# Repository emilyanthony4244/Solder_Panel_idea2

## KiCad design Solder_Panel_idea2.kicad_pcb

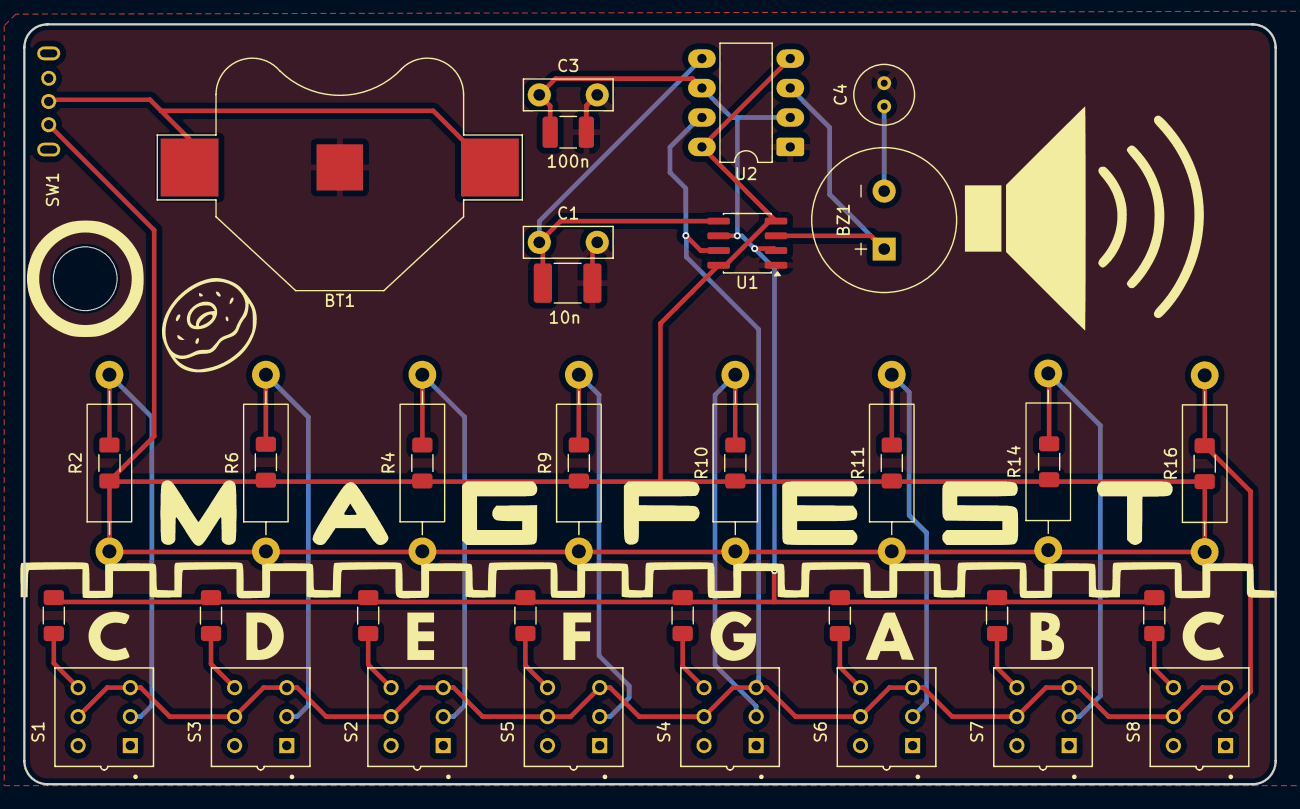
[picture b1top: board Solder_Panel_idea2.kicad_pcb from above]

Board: 2 copper layers, 107.9 x 65.5 mm, 42 parts (0 on the bottom side), 22 nets.

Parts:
BT1: 1043; BatteryHolder_Multicomp_BC-2001_1x2032
BZ1: Buzzer; Buzzer_12.5x7.5
C1: 10n; C_Disc_D7.5mm_W2.5mm_P5.00mm
C2: 100n; C_1210_3225Metric_Pad1.33x2.70mm_HandSolder
C3: 100n; C_Disc_D7.5mm_W2.5mm_P5.00mm
C4: 10u; C_Radial_D5.0mm_H7.0mm_P2.00mm
C5: 10n; C_1812_4532Metric_Pad1.57x3.40mm_HandSolder
R1, R3, R5, R7, R8, R12, R13, R15: 910; R_1206_3216Metric_Pad1.30x1.75mm_HandSolder
R2, R4, R6, R9, R10, R11, R14, R16: 910; R_Axial_DIN0411_L9.9mm_D3.6mm_P15.24mm_Horizontal
R17: 24k; R_1206_3216Metric_Pad1.30x1.75mm_HandSolder
R18: 27k; R_1206_3216Metric_Pad1.30x1.75mm_HandSolder
R19: 22k; R_1206_3216Metric_Pad1.30x1.75mm_HandSolder
R20: 18k; R_1206_3216Metric_Pad1.30x1.75mm_HandSolder
R21: 20k; R_1206_3216Metric_Pad1.30x1.75mm_HandSolder
R22: 16k; R_1206_3216Metric_Pad1.30x1.75mm_HandSolder
R23: 14k; R_1206_3216Metric_Pad1.30x1.75mm_HandSolder
R24: 13.2k; R_1206_3216Metric_Pad1.30x1.75mm_HandSolder
S1, S2, S3, S4, S5, S6, S7, S8: C5379898; SW_5.8WSPT
SW1: SW_SPDT_1825232-1; 1825232-1
U1: ICM7555IBAZ-T; SOIC-8_3.9x4.9mm_P1.27mm
U2: ICM7555IBAZ-T; DIP-8_W7.62mm_LongPads

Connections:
GND: BT1.2, C1.2, C2.2, C3.2, C4.2, C5.2, U1.1 (GND), U2.1 (GND)
unnamed: BZ1.2 (+), C4.1
unnamed: BZ1.1 (-), U1.3 (Q), U2.3 (Q)
unnamed: R1.2, R2.2, S1.2
unnamed: R19.1, S2.6
unnamed: R21.1, S5.6
unnamed: R20.1, S4.6
unnamed: R22.1, S6.6
unnamed: R23.1, S7.6
unnamed: R5.2, R6.2, S3.2
unnamed: R3.2, R4.2, S2.2
unnamed: R7.2, R9.2, S5.2
unnamed: R8.2, R10.2, S4.2
unnamed: R11.2, R13.2, S6.2
unnamed: R12.2, R14.2, S7.2
unnamed: R18.1, S1.6
unnamed: R17.1, S3.6
unnamed: BT1.1, SW1.2 (B)
unnamed: R1.1, R2.1, R3.1, R4.1, R5.1, R6.1, R7.1, R8.1, R9.1, R10.1, R11.1, R12.1, R13.1, R14.1, R15.1, R16.1, SW1.3 (C), U1.4 (R), U1.8 (VCC), U2.4 (R), U2.8 (VCC)
unnamed: C1.1, C5.1, U1.5 (CV), U2.5 (CV)
unnamed: S1.3, S1.5, S2.3, S2.5, S3.3, S3.5, S4.3, S4.5, S5.3, S5.5, S6.3, S6.5, S7.3, S7.5, S8.3, S8.5, U1.7 (DIS), U2.7 (DIS)
unnamed: C2.1, C3.1, R17.2, R18.2, R19.2, R20.2, R21.2, R22.2, R23.2, R24.2, U1.2 (TR), U1.6 (THR), U2.2 (TR), U2.6 (THR)

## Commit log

2025-10-16 Inital Version
2025-12-08 layout changes, art, add 8th note
